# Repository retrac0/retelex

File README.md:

# Retelex

Retro telephone exchange.  Also retro telex exchange.  

# MF8 — a six-channel digital voice carrier in discrete logic

Six 64 kbps channels and a sub-commutated signalling channel in an 8-bit frame,
over one twisted pair, built in 74HC. A channel slot is equivalent to  **DS0**: 64 kbps
and octet-aligned.  

Works with a CVSD voice card (the normal Retelex protocol), a synchronous data card, or a
G.711 PCM stream.

```
[ F ][ C1 ][ C2 ][ C3 ][ S ][ C4 ][ C5 ][ C6 ]      8 bits, 15.625 µs, 64 kHz
                                                    512 kbps, 1.024 MBaud
```

The superframe is a sequence of 8 frames. It carries signalling (one bit per channel at
8 kHz), it carries the framing word, **and it is the octet counter**, so at a
64 kHz frame rate, the superframe rate is 8 kHz, the PCM sample rate exactly, and
one superframe carries one sample.  

But we don't use PCM in practice.  Though byte-boundary support does exist.

# Exchange

Sixty-four line exchange.  Supports MF8 trunks between exchanges.

Up to 48 subscriber lines.  0x and 1x are reserved for trunk and supervisor features.

Anywhere from 1 to 64 lines can be trunks.  Each exchange supports connections
up to four different exchanges, in any number of lines.  For example,
MF8 can be doubled so an exchange has 12 lines tying it to its neighbour.  This 
could be done on two fronts for a total of 24 tie lines.

The directions are labelled after the compass points NSEW but this is purely
notional.

Digital switching, CVSD or data.

Pulse flood protocol.  Sending exchange calls all outward directions which is
passed on by all exchanges until dropped or accepted.  Preliminary traffic
simulation suggests this scales to about a thousand lines across a few dozen
exchanges.

General purpose architecture.  Chains, stars and rings are possible.

## Layout

```
common/     the cards, and everything that belongs to neither shelf nor block
mf8/        the MF8 carrier: frame, line, backplane
exchange/   the exchange: the design as built, proposed/, analysis/
newimpl/    the exchange in Verilog, the reference the documents describe
pcb/        KiCad boards: the block header, the port card, the bus, SU-1, the lamp panel
sim/        every model, and the committed run beside each
falstad/    the voice path as Falstad circuits
spice/      analog circuits in ngspice
mf2/        MF2, the two-channel member of the MF8 family
old/        retired trees (old/verilog)
```

A card plugs into an MF8 shelf or an exchange block unchanged, so its
specification belongs to neither: `common/` is that, and it is why the split
exists. Run the models from the repo root — `python3 sim/mf8.py`.

## Documents

**common/** — the cards, the socket they share, and the line to the telephone

| | |
|---|---|
| [common/terms.md](common/terms.md) | one name per object, and what not to call it |
| [common/clocks.md](common/clocks.md) | every clock in MF8 and in the exchange: one 4.096 MHz crystal, its taps, three domains; no card makes a clock |
| [common/common-cards.md](common/common-cards.md) | the channel socket: pins by card, on an MF8 shelf and on a block's J4; rails; the FXO's one jumper; connectors |
| [common/channel-cards.md](common/channel-cards.md) | the channel cards: the CVSD subscriber line card, the analog FXS/FXO card, the data card; signalling through the A bit, measured |
| [common/subscriber-line.md](common/subscriber-line.md) | the subscriber line: raw CVSD four-wire, hook and ring as held bit patterns, dialling as the line card sees it; the phone is loop-timed |
| [common/tones.md](common/tones.md) | the tone plan and the tone cards: the warble for *progressing*, the buzz for *stop*, the ROM planes, the analog card, the MF8 tone bus |
| [common/cvsd-codec.md](common/cvsd-codec.md) | the CVSD codec circuit and its riser |
| [common/su-1.md](common/su-1.md) | SU-1 subscriber set: native CVSD, 4P4C handset, Autovon pad → dial pulses, three boards (SU-D / SU-A / SU-K) |
| [common/sdu-1.md](common/sdu-1.md) | SDU-1 data set: 32 kb/s insert-1 on the raw line (switched); RAW64 for nailed 64 kb/s |
| [common/stu-1.md](common/stu-1.md) | STU-1 test set: the lineman's butt set — a lamp field that names the fault, a violation counter on real copper, the phantom in volts |
| [common/subscriber-adapter.md](common/subscriber-adapter.md) | a stock dial telephone on that line: where the 2-wire conversion sits, the adapter, its ringing and its power budget |

**mf8/** — the carrier

| | |
|---|---|
| [mf8/mf8-spec.md](mf8/mf8-spec.md) | MF8 specification — line frame, F word, framer, cards, line code, circuits |
| [mf8/mf8-backplane.md](mf8/mf8-backplane.md) | MF8 shelf backplane — six channel slots, slot interface, three clock domains and where they meet, and the measured cost of the plesiochronous slip |
| [mf8/mf8-psu.md](mf8/mf8-psu.md) | MF8 shelf power: 15–18 V in, regulated −48 V talk battery and ~80 Vrms / 20 Hz ring as two converter paths, split across noisy and quiet 100 × 100 end boards |
| [mf8/mf8-trunk.md](mf8/mf8-trunk.md) | MF8 trunk split: Trunk-D / Trunk-A on 100 × 100, classifier on A, pass-header pinout |
| [mf8/mf8-pico.md](mf8/mf8-pico.md) | the Pico adapter: host gateway to Asterisk, trunk and channel emulator, reference line terminal — the model as an instrument for the breadboard; the receiver's timing grid, measured |
| [mf8/line-codes.md](mf8/line-codes.md) | nine line codes explored; differential Manchester against AMI |
| [mf8/frame-rate.md](mf8/frame-rate.md) | what the frame rate should be: reach against quality, capacity and DS0 |
| [mf8/mfspec.md](mf8/mfspec.md) | the predecessor this design replaced the F word of |

**exchange/**, **newimpl/**, **falstad/**

| | |
|---|---|
| [exchange/](exchange/README.md) | **the exchange**: 64 ports, the pulse flood; the design as built, what is proposed, the analysis behind it, the glossary and the open questions |
| [newimpl/](newimpl/README.md) | the exchange in Verilog: `rtl/`, `tb/`, the benches and the fault list; the reference the documents describe |
| [falstad/](falstad/README.md) | the voice path as Falstad circuits built from subcircuit modules: CVSD encoder, differential Manchester, a line with noise and impulses, the receiver and its recovered clock, the decoder; what to try, and how each matches the model |

## Tools

| | |
|---|---|
| `mf8.py` | reference model and frame-layer battery — the F word, false locks, superframe phase, where S sits, slot rules over every byte in every seat, line errors, slip recovery |
| `mf8_line.py` | end to end: six independent talkers, real CVSD, a real waveform, both line codes |
| `linecodes.py` | the line itself — which code, how it fails, what the rate costs |
| `impulse_sweep.py` | the impulse falloff curve: 23 rates, both codes, error bars, thresholds |
| `mf8_render.py` | renders 15 s of every channel to `sim/out/` under nine line conditions in both codes, for listening |
| `subline.py` | the subscriber line: CVSD against the held patterns, the hook and ring detectors, dial pulses as the line card sees them, the register end to end, DTMF through the codec |
| `cvsd_law.py` | the codec law: MIL-STD-188-113 read from the standard's own test patterns, against the previous law, whether it is bit-rate specific, and a DNVT on a 64 kbps channel |
| `tolerance.py` | CVSD encoder/decoder component-mismatch tolerance at 64 kbps, `I_min` included |
| `falstad_cvsd.py` | builds the Falstad (CircuitJS) modules and the three circuits in `falstad/` from the codec law and the line constants; and `check`, which compares a Falstad run with `cvsd.py` and `fast.mono_decode` |
| `falstad/sim.mjs` | runs a circuit in falstad.com's simulator in headless Chromium and records every labeled node, for that check |
| `audio.py` `cvsd.py` `phy.py` `fast.py` | shared: audio I/O and scoring, the CVSD codec, the physical layer, C-accelerated inner loops |
| `talkers.py` | builds the seven independent test talkers from LibriSpeech |
| `tones.py` | call-progress tones as looped CVSD: the shortest seamless loop, what ROM depth buys, eight tone plans compared, five ways to make a warble, and the cadence as a binary divide. Renders the plan to `sim/out/` |
| `exch.py` | the exchange: the fabric cell by cell, calls a millisecond at a time, the flood across a network, traffic. `exchange/README.md` §4 lists its runs |

```
python3 sim/mf8.py            frame layer (8-bit / 6 ch)  (mf8.log)
python3 sim/mf8_line.py       over the line              (mf8_line.log)
# measured, not taken: mf8_16.py, mf8_10.py, mf8_10_16.py, mf8_baud.py
python3 sim/linecodes.py      line codes and rate  (linecodes.log)
python3 sim/impulse_sweep.py  impulse falloff      (impulse_sweep.log, .csv)
python3 sim/mf8_render.py     listenable renders   (mf8_render.log; wavs in out/)
python3 sim/subline.py        subscriber line      (subline.log)
python3 sim/cvsd_law.py       the codec law        (cvsd_law.log)
python3 sim/tolerance.py      codec tolerances     (tolerance.log)
python3 sim/tones.py          call-progress tones   (tones.log; wavs in sim/out/)
python3 sim/falstad_cvsd.py   Falstad prototypes   (falstad_cvsd.log; falstad/*.txt)
```

`sim/out/` is not committed. Each render is the full 15 s as the link delivers it —
muted wherever the framer was not locked, so outages are heard in place rather
than edited out. Files are `{dm,ami}_{condition}_ch{n}.wav`, with
`source_ch{n}.wav` as the reference.

The `.log` files beside each in `sim/` are the committed runs. Every table in
the documents is reproducible from them.

## Test audio

`sim/talker1.wav` … `sim/talker7.wav` are seven independent LibriSpeech dev-clean
speakers, 30 s each, and are **not committed** — they are extracts from
third-party material. Rebuild them with `python3 sim/talkers.py --root <dev-clean>`.
`sim/phy_fast.c` builds to `sim/libphyfast.so`; see the header of `fast.py`.

## What is settled and what is not

Settled: the frame, the F word, the framer, and that the carrier is transparent —
six talkers through the whole chain in both line codes add **+0.00 dB**.

Not settled, and not settleable here: **the impulse rate on the target loops.**
The curve is measured (`impulse_sweep.py`, `mf8/line-codes.md` §4.5): each
impulse costs differential Manchester about 0.77 breaks and AMI about 0.14, so
differential Manchester reaches one click a second at 1.3 impulses/s and AMI at
about 8. AMI holds that advantage until it collapses outright between 800 and 900
impulses/s. Which matters depends on the loop, and that is a counter on a real
pair.

## Todo

* Hook flash - put the call on hold!  Implemented probably in the subscriber card
  When on hold the keypad could become available

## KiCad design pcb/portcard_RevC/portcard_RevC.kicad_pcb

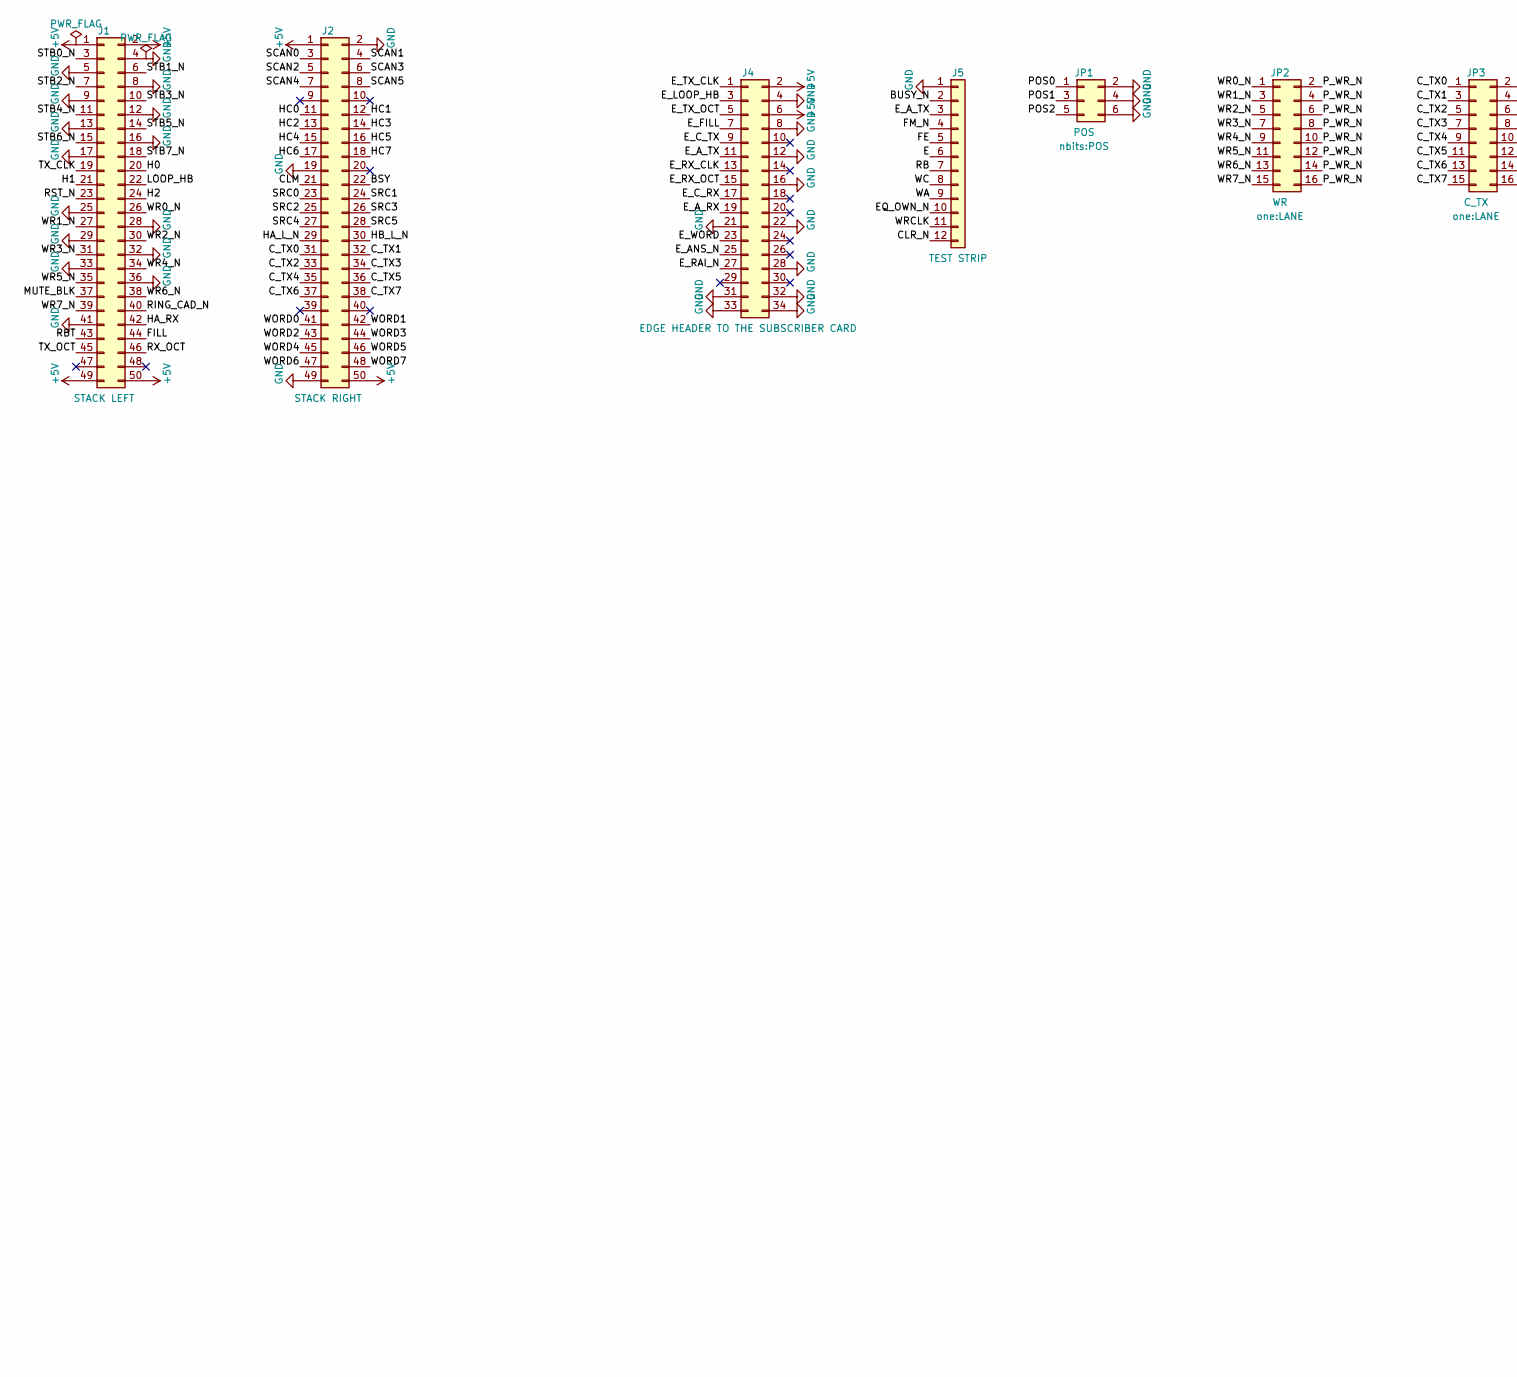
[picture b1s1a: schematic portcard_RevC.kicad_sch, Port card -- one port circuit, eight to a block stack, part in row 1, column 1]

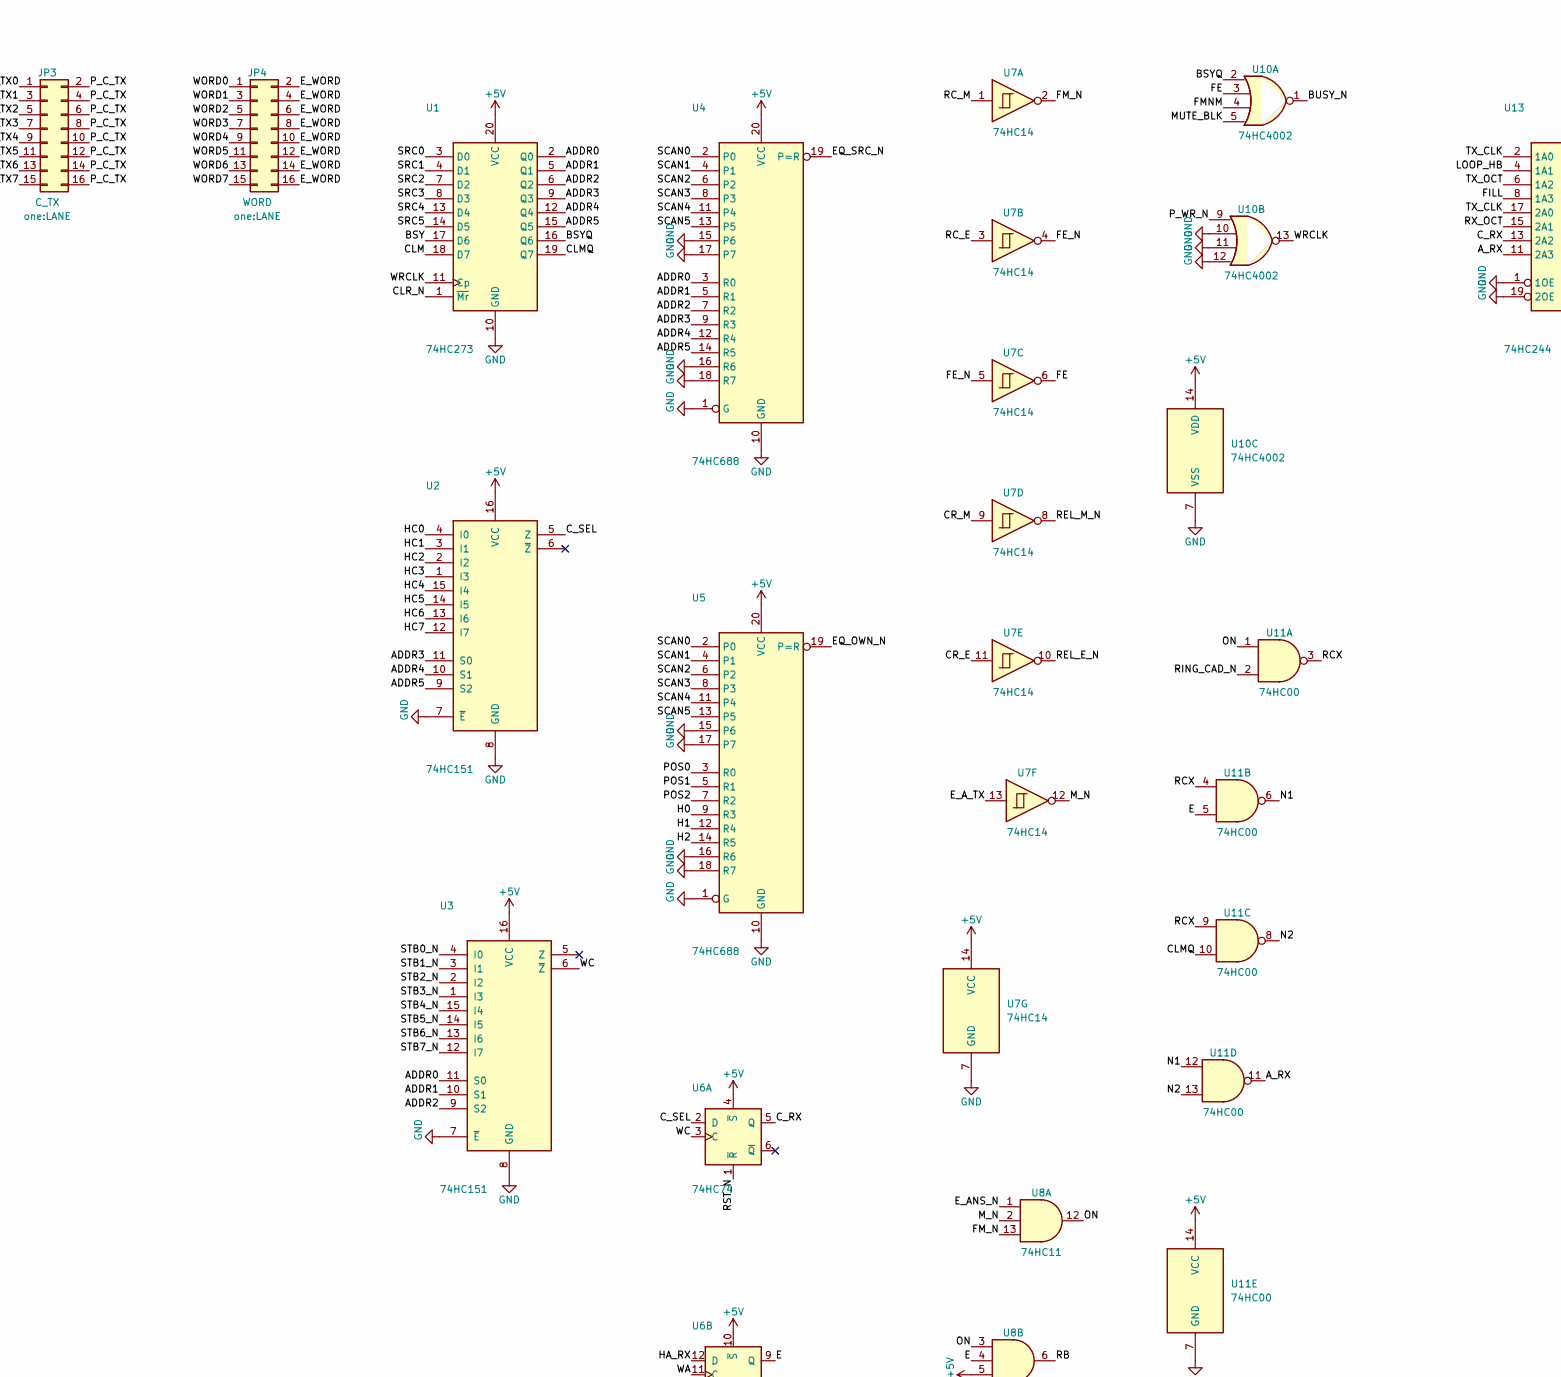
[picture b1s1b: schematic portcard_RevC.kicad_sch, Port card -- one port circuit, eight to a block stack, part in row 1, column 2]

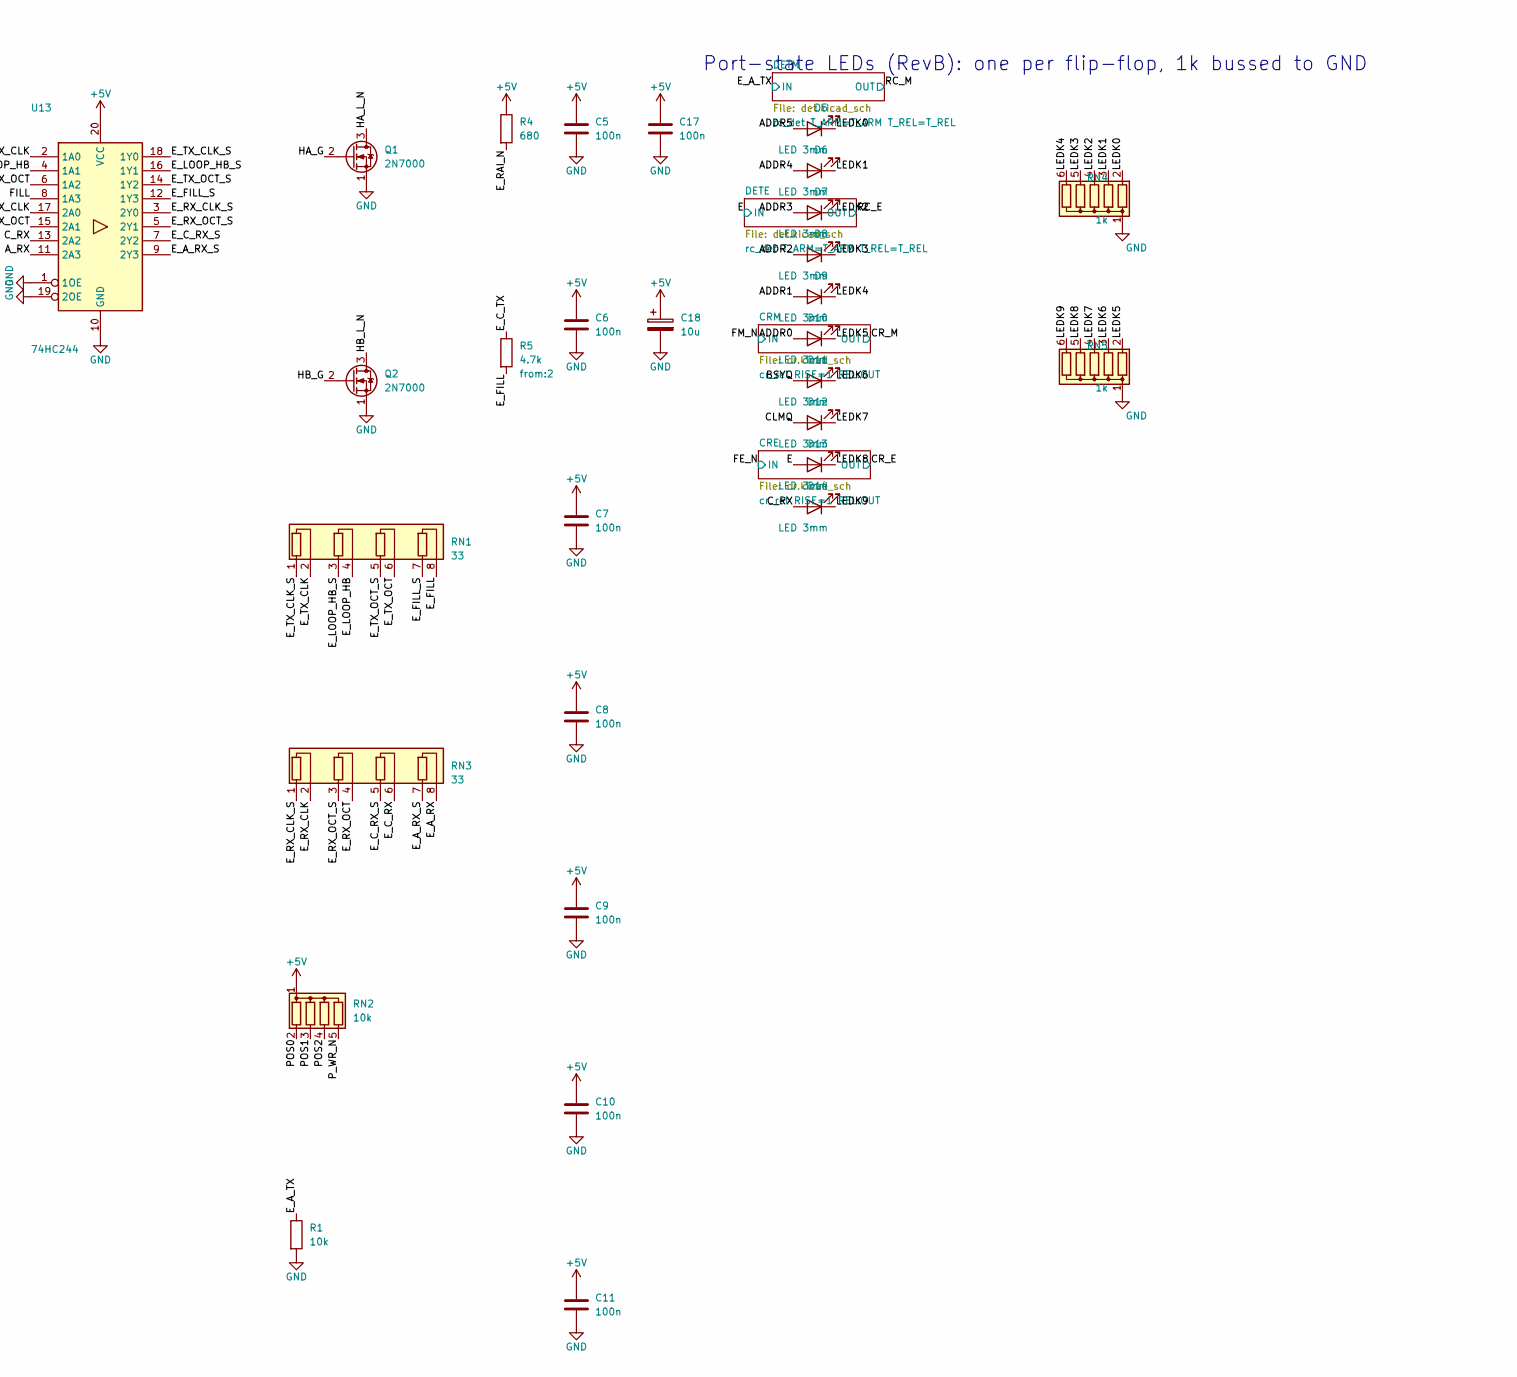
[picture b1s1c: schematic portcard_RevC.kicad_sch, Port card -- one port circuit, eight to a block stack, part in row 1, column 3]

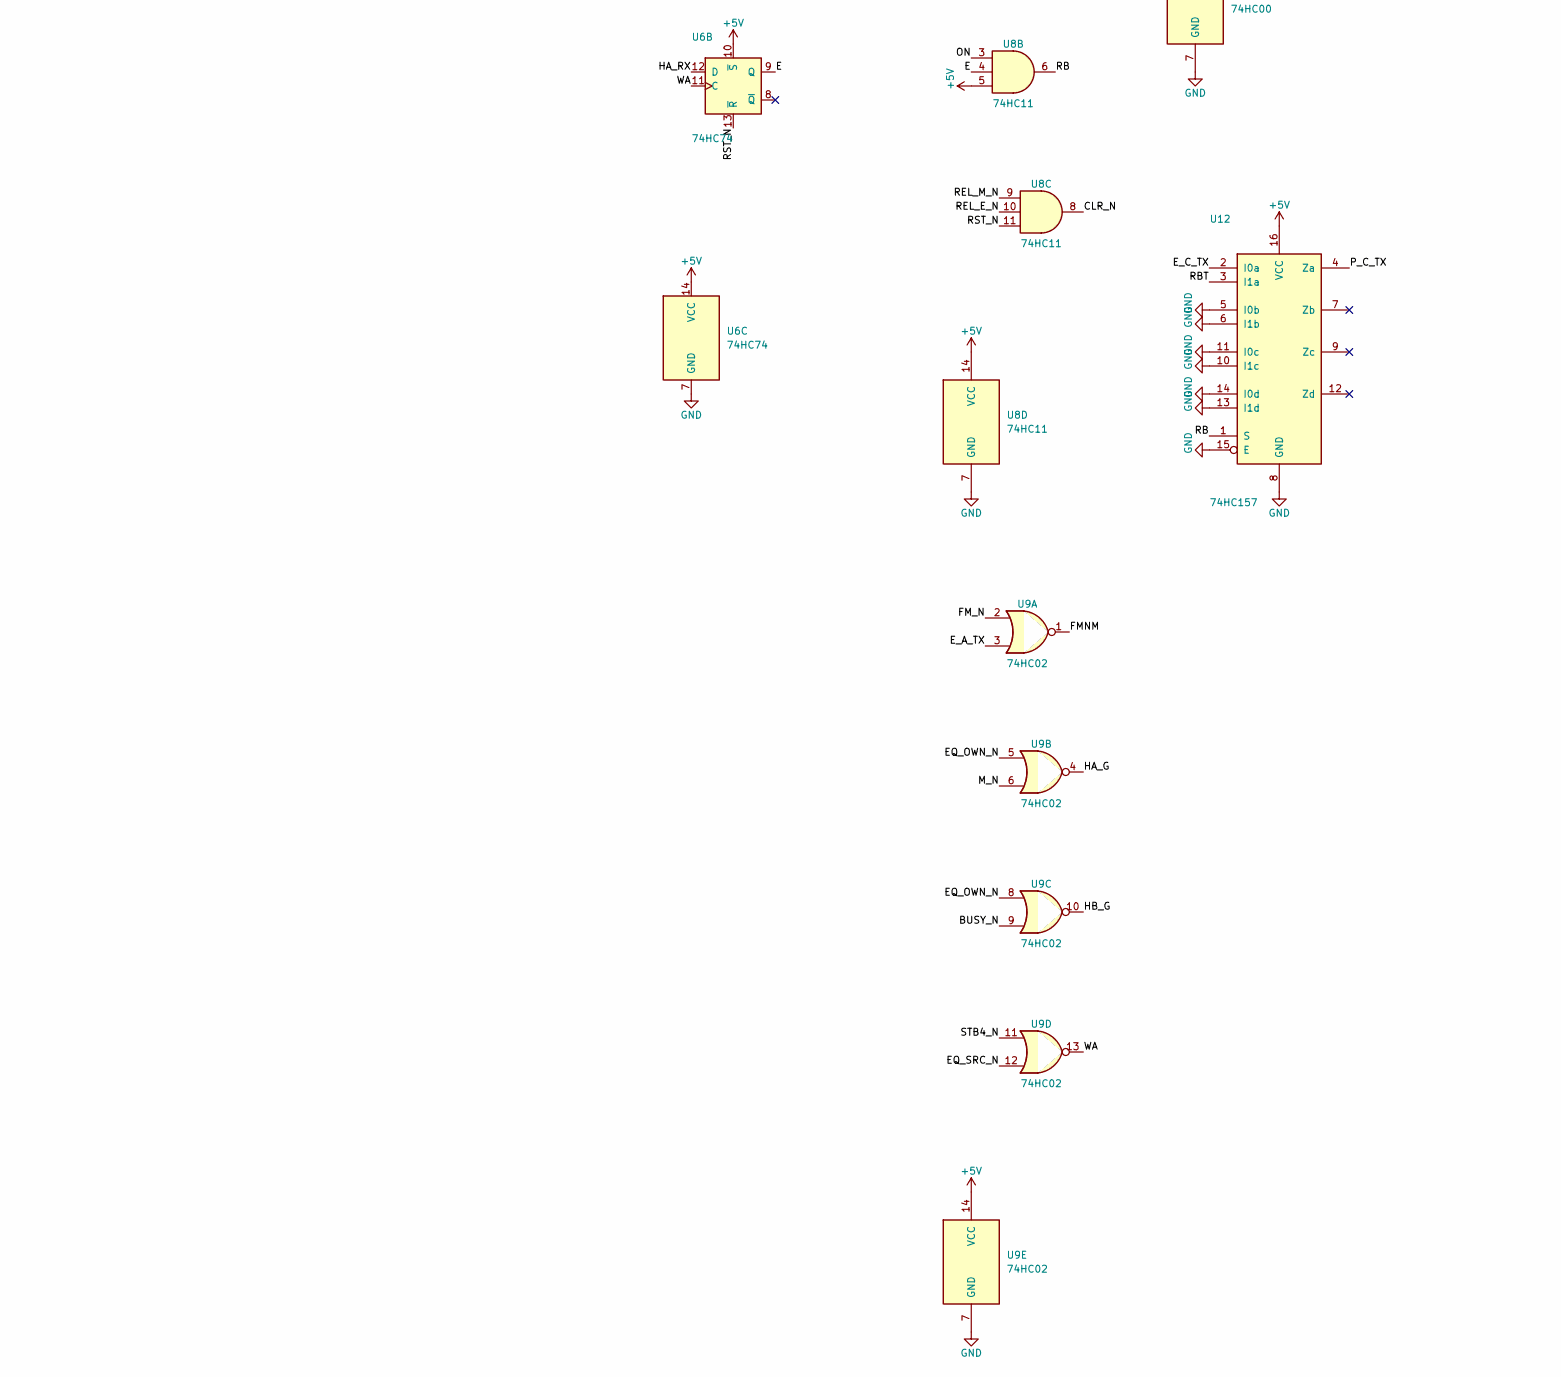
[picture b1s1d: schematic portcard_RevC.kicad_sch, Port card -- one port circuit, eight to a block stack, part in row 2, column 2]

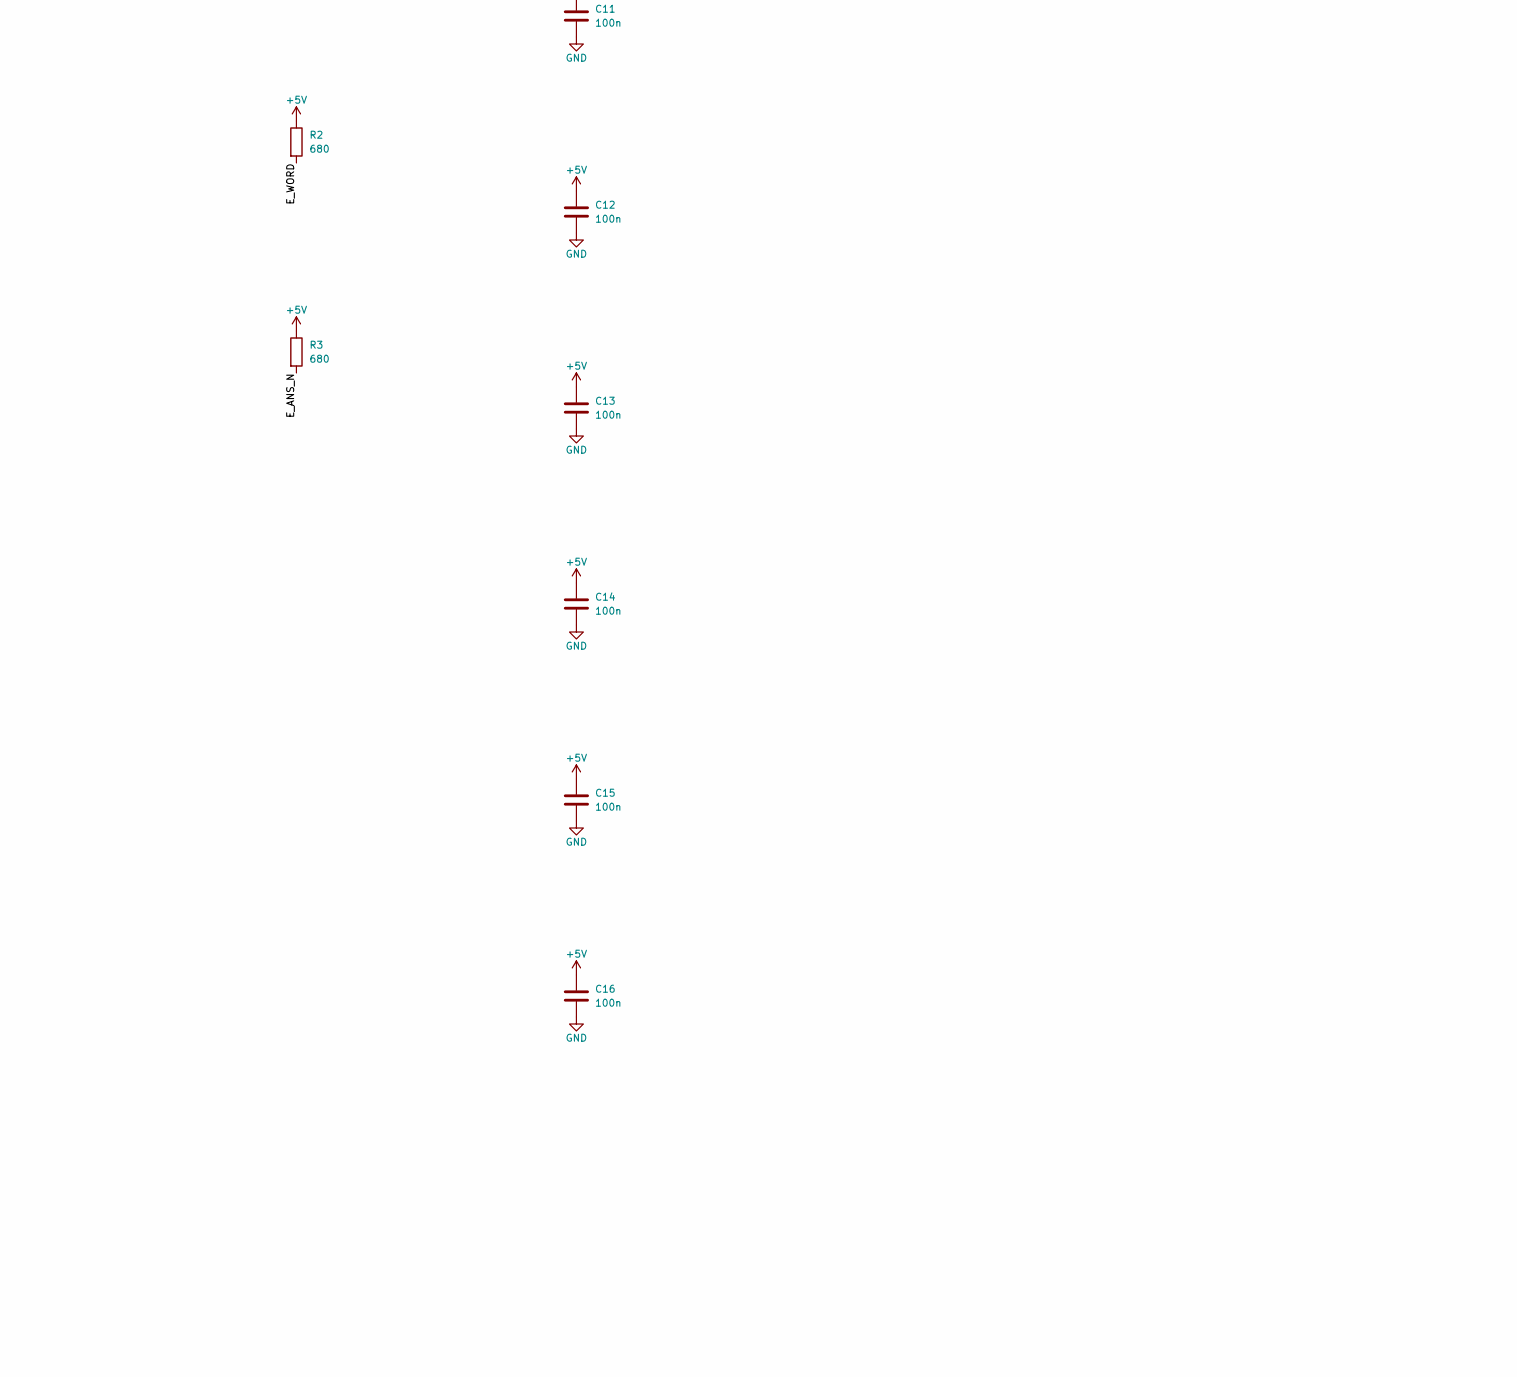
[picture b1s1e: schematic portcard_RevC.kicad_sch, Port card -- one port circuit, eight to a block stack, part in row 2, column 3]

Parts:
C5, C6, C7, C8, C9, C10, C11, C12, C13, C14, C15, C16, C17: 100n; C_Disc_D3.0mm_W1.6mm_P2.50mm
C18: 10u; CP_Radial_D4.0mm_P1.50mm
D5, D6, D7, D8, D9, D10, D11, D12, D13, D14: LED 3mm; LED_D3.0mm_Row
J1: STACK LEFT; Stack_2x25_P2.54mm_LongTail
J2: STACK RIGHT; Stack_2x25_P2.54mm_LongTail
J4: EDGE HEADER TO THE SUBSCRIBER CARD; IDC-Header_2x17_P2.54mm_Horizontal
J5: TEST STRIP; PinHeader_1x12_P2.54mm_Horizontal
JP1: POS; PinHeader_2x03_P2.54mm_Vertical
JP2: WR; PinHeader_2x08_P2.54mm_Vertical
JP3: C_TX; PinHeader_2x08_P2.54mm_Vertical
JP4: WORD; PinHeader_2x08_P2.54mm_Vertical
Q1, Q2: 2N7000; TO-92_Inline
R1: 10k; R_Axial_DIN0207_L6.3mm_D2.5mm_P2.54mm_Vertical
R2, R3, R4: 680; R_Axial_DIN0207_L6.3mm_D2.5mm_P2.54mm_Vertical
R5: 4.7k; R_Axial_DIN0207_L6.3mm_D2.5mm_P2.54mm_Vertical
RN1, RN3: 33; R_Array_SIP8
RN2: 10k; R_Array_SIP5
RN4, RN5: 1k; R_Array_SIP6
U1: 74HC273; DIP-20_W7.62mm
U2, U3: 74HC151; DIP-16_W7.62mm
U4, U5: 74HC688; DIP-20_W7.62mm
U6: 74HC74; DIP-14_W7.62mm
U7: 74HC14; DIP-14_W7.62mm
U8: 74HC11; DIP-14_W7.62mm
U9: 74HC02; DIP-14_W7.62mm
U10: 74HC4002; DIP-14_W7.62mm
U11: 74HC00; DIP-14_W7.62mm
U12: 74HC157; DIP-16_W7.62mm
U13: 74HC244; DIP-20_W7.62mm

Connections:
+5V: C5.1, C6.1, C7.1, C8.1, C9.1, C10.1, C11.1, C12.1, C13.1, C14.1, C15.1, C16.1, C17.1, C18.1, J1.1, J1.2, J1.49, J1.50, J2.1, J2.50, J4.2, J4.6, R2.1, R3.1, R4.1, RN2.1 (common), U1.20 (VCC), U2.16 (VCC), U3.16 (VCC), U4.20 (VCC), U5.20 (VCC), U6.4 (~S), U6.10 (~S), U6.14 (VCC), U7.14 (VCC), U8.5, U8.14 (VCC), U9.14 (VCC), U10.14 (VDD), U11.14 (VCC), U12.16 (VCC), U13.20 (VCC)
/ADDR0: D10.2 (A), U1.2 (Q0), U3.11 (S0), U4.3 (R0)
/ADDR1: D9.2 (A), U1.5 (Q1), U3.10 (S1), U4.5 (R1)
/ADDR2: D8.2 (A), U1.6 (Q2), U3.9 (S2), U4.7 (R2)
/ADDR3: D7.2 (A), U1.9 (Q3), U2.11 (S0), U4.9 (R3)
/ADDR4: D6.2 (A), U1.12 (Q4), U2.10 (S1), U4.12 (R4)
/ADDR5: D5.2 (A), U1.15 (Q5), U2.9 (S2), U4.14 (R5)
/A_RX: U11.11, U13.11 (2A3)
/BSY: J2.22, U1.17 (D6)
/BSYQ: D11.2 (A), U1.16 (Q6), U10.2
/BUSY_N: J5.2, U9.9, U10.1
/CLM: J2.21, U1.18 (D7)
/CLMQ: D12.2 (A), U1.19 (Q7), U11.10
/CLR_N: J5.12, U1.1 (~Mr), U8.8
/CR_E: U7.11; also elsewhere on the board
/CR_M: U7.9; also elsewhere on the board
/C_RX: D14.2 (A), U6.5 (Q), U13.13 (2A2)
/C_SEL: U2.5 (Z), U6.2 (D)
/C_TX0: J2.31, JP3.1
/C_TX1: J2.32, JP3.3
/C_TX2: J2.33, JP3.5
/C_TX3: J2.34, JP3.7
/C_TX4: J2.35, JP3.9
/C_TX5: J2.36, JP3.11
/C_TX6: J2.37, JP3.13
/C_TX7: J2.38, JP3.15
/E: D13.2 (A), J5.6, U6.9 (Q), U8.4, U11.5; also elsewhere on the board
/EQ_OWN_N: J5.10, U5.19 (P=R), U9.5, U9.8
/EQ_SRC_N: U4.19 (P=R), U9.12
/E_ANS_N: J4.25, R3.2, U8.1
/E_A_RX: J4.19, RN3.8 (R4.2)
/E_A_RX_S: RN3.7 (R4.1), U13.9 (2Y3)
/E_A_TX: J4.11, J5.3, R1.1, U7.13, U9.3; also elsewhere on the board
/E_C_RX: J4.17, RN3.6 (R3.2)
/E_C_RX_S: RN3.5 (R3.1), U13.7 (2Y2)
/E_C_TX: J4.9, R5.1, U12.2 (I0a)
/E_FILL: J4.7, R5.2, RN1.8 (R4.2)
/E_FILL_S: RN1.7 (R4.1), U13.12 (1Y3)
/E_LOOP_HB: J4.3, RN1.4 (R2.2)
/E_LOOP_HB_S: RN1.3 (R2.1), U13.16 (1Y1)
/E_RAI_N: J4.27, R4.2
/E_RX_CLK: J4.13, RN3.2 (R1.2)
/E_RX_CLK_S: RN3.1 (R1.1), U13.3 (2Y0)
/E_RX_OCT: J4.15, RN3.4 (R2.2)
/E_RX_OCT_S: RN3.3 (R2.1), U13.5 (2Y1)
/E_TX_CLK: J4.1, RN1.2 (R1.2)
/E_TX_CLK_S: RN1.1 (R1.1), U13.18 (1Y0)
/E_TX_OCT: J4.5, RN1.6 (R3.2)
/E_TX_OCT_S: RN1.5 (R3.1), U13.14 (1Y2)
/E_WORD: J4.23, JP4.2, JP4.4, JP4.6, JP4.8, JP4.10, JP4.12, JP4.14, JP4.16, R2.2
/FE: J5.5, U7.6, U10.3
/FE_N: U7.4, U7.5; also elsewhere on the board
/FILL: J1.44, U13.8 (1A3)
/FMNM: U9.1, U10.4
/FM_N: J5.4, U7.2, U8.13, U9.2; also elsewhere on the board
/H0: J1.20, U5.9 (R3)
/H1: J1.21, U5.12 (R4)
/H2: J1.24, U5.14 (R5)
/HA_G: Q1.2 (G), U9.4
/HA_L_N: J2.29, Q1.3 (D)
/HA_RX: J1.42, U6.12 (D)
/HB_G: Q2.2 (G), U9.10
/HB_L_N: J2.30, Q2.3 (D)
/HC0: J2.11, U2.4 (I0)
/HC1: J2.12, U2.3 (I1)
/HC2: J2.13, U2.2 (I2)
/HC3: J2.14, U2.1 (I3)
/HC4: J2.15, U2.15 (I4)
/HC5: J2.16, U2.14 (I5)
/HC6: J2.17, U2.13 (I6)
/HC7: J2.18, U2.12 (I7)
/LEDK0: D5.1 (K), RN4.2 (R1)
/LEDK1: D6.1 (K), RN4.3 (R2)
/LEDK2: D7.1 (K), RN4.4 (R3)
/LEDK3: D8.1 (K), RN4.5 (R4)
/LEDK4: D9.1 (K), RN4.6 (R5)
/LEDK5: D10.1 (K), RN5.2 (R1)
/LEDK6: D11.1 (K), RN5.3 (R2)
/LEDK7: D12.1 (K), RN5.4 (R3)
/LEDK8: D13.1 (K), RN5.5 (R4)
/LEDK9: D14.1 (K), RN5.6 (R5)
/LOOP_HB: J1.22, U13.4 (1A1)
/MUTE_BLK: J1.37, U10.5
/M_N: U7.12, U8.2, U9.6
/N1: U11.6, U11.12
/N2: U11.8, U11.13
/ON: U8.3, U8.12, U11.1
/POS0: JP1.1, RN2.2 (R1), U5.3 (R0)
/POS1: JP1.3, RN2.3 (R2), U5.5 (R1)
/POS2: JP1.5, RN2.4 (R3), U5.7 (R2)
/P_C_TX: JP3.2, JP3.4, JP3.6, JP3.8, JP3.10, JP3.12, JP3.14, JP3.16, U12.4 (Za)
/P_WR_N: JP2.2, JP2.4, JP2.6, JP2.8, JP2.10, JP2.12, JP2.14, JP2.16, RN2.5 (R4), U10.9
/RB: J5.7, U8.6, U12.1 (S)
/RBT: J1.43, U12.3 (I1a)
/RCX: U11.3, U11.4, U11.9
/RC_E: U7.3; also elsewhere on the board
/RC_M: U7.1; also elsewhere on the board
/REL_E_N: U7.10, U8.10
/REL_M_N: U7.8, U8.9
/RING_CAD_N: J1.40, U11.2
/RST_N: J1.23, U6.1 (~R), U6.13 (~R), U8.11
/RX_OCT: J1.46, U13.15 (2A1)
/SCAN0: J2.3, U4.2 (P0), U5.2 (P0)
/SCAN1: J2.4, U4.4 (P1), U5.4 (P1)
/SCAN2: J2.5, U4.6 (P2), U5.6 (P2)
/SCAN3: J2.6, U4.8 (P3), U5.8 (P3)
/SCAN4: J2.7, U4.11 (P4), U5.11 (P4)
/SCAN5: J2.8, U4.13 (P5), U5.13 (P5)
/SRC0: J2.23, U1.3 (D0)
/SRC1: J2.24, U1.4 (D1)
/SRC2: J2.25, U1.7 (D2)
/SRC3: J2.26, U1.8 (D3)
/SRC4: J2.27, U1.13 (D4)
/SRC5: J2.28, U1.14 (D5)
/STB0_N: J1.3, U3.4 (I0)
/STB1_N: J1.6, U3.3 (I1)
/STB2_N: J1.7, U3.2 (I2)
/STB3_N: J1.10, U3.1 (I3)
/STB4_N: J1.11, U3.15 (I4), U9.11
/STB5_N: J1.14, U3.14 (I5)
/STB6_N: J1.15, U3.13 (I6)
/STB7_N: J1.18, U3.12 (I7)
/TX_CLK: J1.19, U13.2 (1A0), U13.17 (2A0)
/TX_OCT: J1.45, U13.6 (1A2)
/WA: J5.9, U6.11 (C), U9.13
/WC: J5.8, U3.6 (~Z), U6.3 (C)
/WORD0: J2.41, JP4.1
/WORD1: J2.42, JP4.3
/WORD2: J2.43, JP4.5
/WORD3: J2.44, JP4.7
/WORD4: J2.45, JP4.9
/WORD5: J2.46, JP4.11
/WORD6: J2.47, JP4.13
/WORD7: J2.48, JP4.15
/WR0_N: J1.26, JP2.1
/WR1_N: J1.27, JP2.3
/WR2_N: J1.30, JP2.5
/WR3_N: J1.31, JP2.7
/WR4_N: J1.34, JP2.9
/WR5_N: J1.35, JP2.11
/WR6_N: J1.38, JP2.13
/WR7_N: J1.39, JP2.15
/WRCLK: J5.11, U1.11 (Cp), U10.13
GND: C5.2, C6.2, C7.2, C8.2, C9.2, C10.2, C11.2, C12.2, C13.2, C14.2, C15.2, C16.2, C17.2, C18.2, J1.4, J1.5, J1.8, J1.9, J1.12, J1.13, J1.16, J1.17, J1.25, J1.28, J1.29, J1.32, J1.33, J1.36, J1.41, J2.2, J2.19, J2.49, J4.4, J4.8, J4.12, J4.16, J4.21, J4.22, J4.28, J4.31, J4.32, J4.33, J4.34, J5.1, JP1.2, JP1.4, JP1.6, Q1.1 (S), Q2.1 (S), R1.2, RN4.1 (common), RN5.1 (common), U1.10 (GND), U2.7 (~E), U2.8 (GND), U3.7 (~E), U3.8 (GND), U4.1 (G), U4.10 (GND), U4.15 (P6), U4.16 (R6), U4.17 (P7), U4.18 (R7), U5.1 (G), U5.10 (GND), U5.15 (P6), U5.16 (R6), U5.17 (P7), U5.18 (R7), U6.7 (GND), U7.7 (GND), U8.7 (GND), U9.7 (GND), U10.7 (VSS), U10.10, U10.11, U10.12, U11.7 (GND), U12.5 (I0b), U12.6 (I1b), U12.8 (GND), U12.10 (I1c), U12.11 (I0c), U12.13 (I1d), U12.14 (I0d), U12.15 (E), U13.1 (1OE), U13.10 (GND), U13.19 (2OE); also elsewhere on the board

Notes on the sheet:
Port-state LEDs (RevB): one per flip-flop, 1k bussed to GND

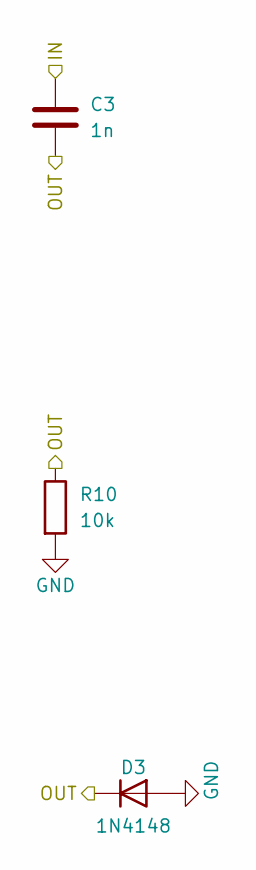
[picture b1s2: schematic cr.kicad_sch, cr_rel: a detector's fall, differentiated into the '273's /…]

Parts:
C3: 1n; C_Disc_D5.0mm_W2.5mm_P2.50mm
D3: 1N4148; D_DO-35_SOD27_P2.54mm_Vertical_AnodeUp
R10: 10k; R_Axial_DIN0207_L6.3mm_D2.5mm_P2.54mm_Vertical

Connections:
/CR_M: C3.2, D3.1 (K), R10.1; also elsewhere on the board
/FM_N: C3.1; also elsewhere on the board
GND: D3.2 (A), R10.2; also elsewhere on the board

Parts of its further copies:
C4: 1n; C_Disc_D5.0mm_W2.5mm_P2.50mm
D4: 1N4148; D_DO-35_SOD27_P2.54mm_Vertical_AnodeUp
R11: 10k; R_Axial_DIN0207_L6.3mm_D2.5mm_P2.54mm_Vertical

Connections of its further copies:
/CR_E: C4.2, D4.1 (K), R11.1; also elsewhere on the board
/FE_N: C4.1; also elsewhere on the board
GND: D4.2 (A), R11.2; also elsewhere on the board

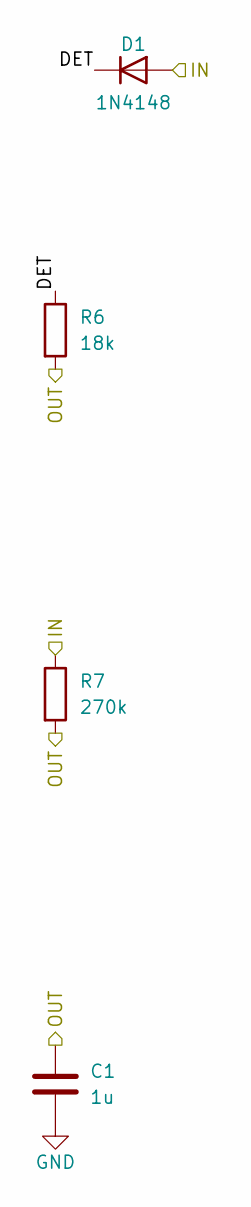
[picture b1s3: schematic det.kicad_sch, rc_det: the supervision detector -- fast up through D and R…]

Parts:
C1: 1u; C_Rect_L7.2mm_W3.5mm_P5.00mm_FKS2_FKP2_MKS2_MKP2
D1: 1N4148; D_DO-35_SOD27_P2.54mm_Vertical_AnodeUp
R6: 18k; R_Axial_DIN0207_L6.3mm_D2.5mm_P2.54mm_Vertical
R7: 270k; R_Axial_DIN0207_L6.3mm_D2.5mm_P2.54mm_Vertical

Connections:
/DETM/DET: D1.1 (K), R6.1
/E_A_TX: D1.2 (A), R7.1; also elsewhere on the board
/RC_M: C1.1, R6.2, R7.2; also elsewhere on the board
GND: C1.2; also elsewhere on the board

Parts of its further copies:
C2: 1u; C_Rect_L7.2mm_W3.5mm_P5.00mm_FKS2_FKP2_MKS2_MKP2
D2: 1N4148; D_DO-35_SOD27_P2.54mm_Vertical_AnodeUp
R8: 18k; R_Axial_DIN0207_L6.3mm_D2.5mm_P2.54mm_Vertical
R9: 270k; R_Axial_DIN0207_L6.3mm_D2.5mm_P2.54mm_Vertical

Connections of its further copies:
/DETE/DET: D2.1 (K), R8.1
/E: D2.2 (A), R9.1; also elsewhere on the board
/RC_E: C2.1, R8.2, R9.2; also elsewhere on the board
GND: C2.2; also elsewhere on the board

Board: 2 copper layers, 75 parts (0 on the bottom side), 146 nets, no tracks yet.

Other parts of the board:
H1, H2, H3, H4: M3; MountingHole_3.2mm_M3
